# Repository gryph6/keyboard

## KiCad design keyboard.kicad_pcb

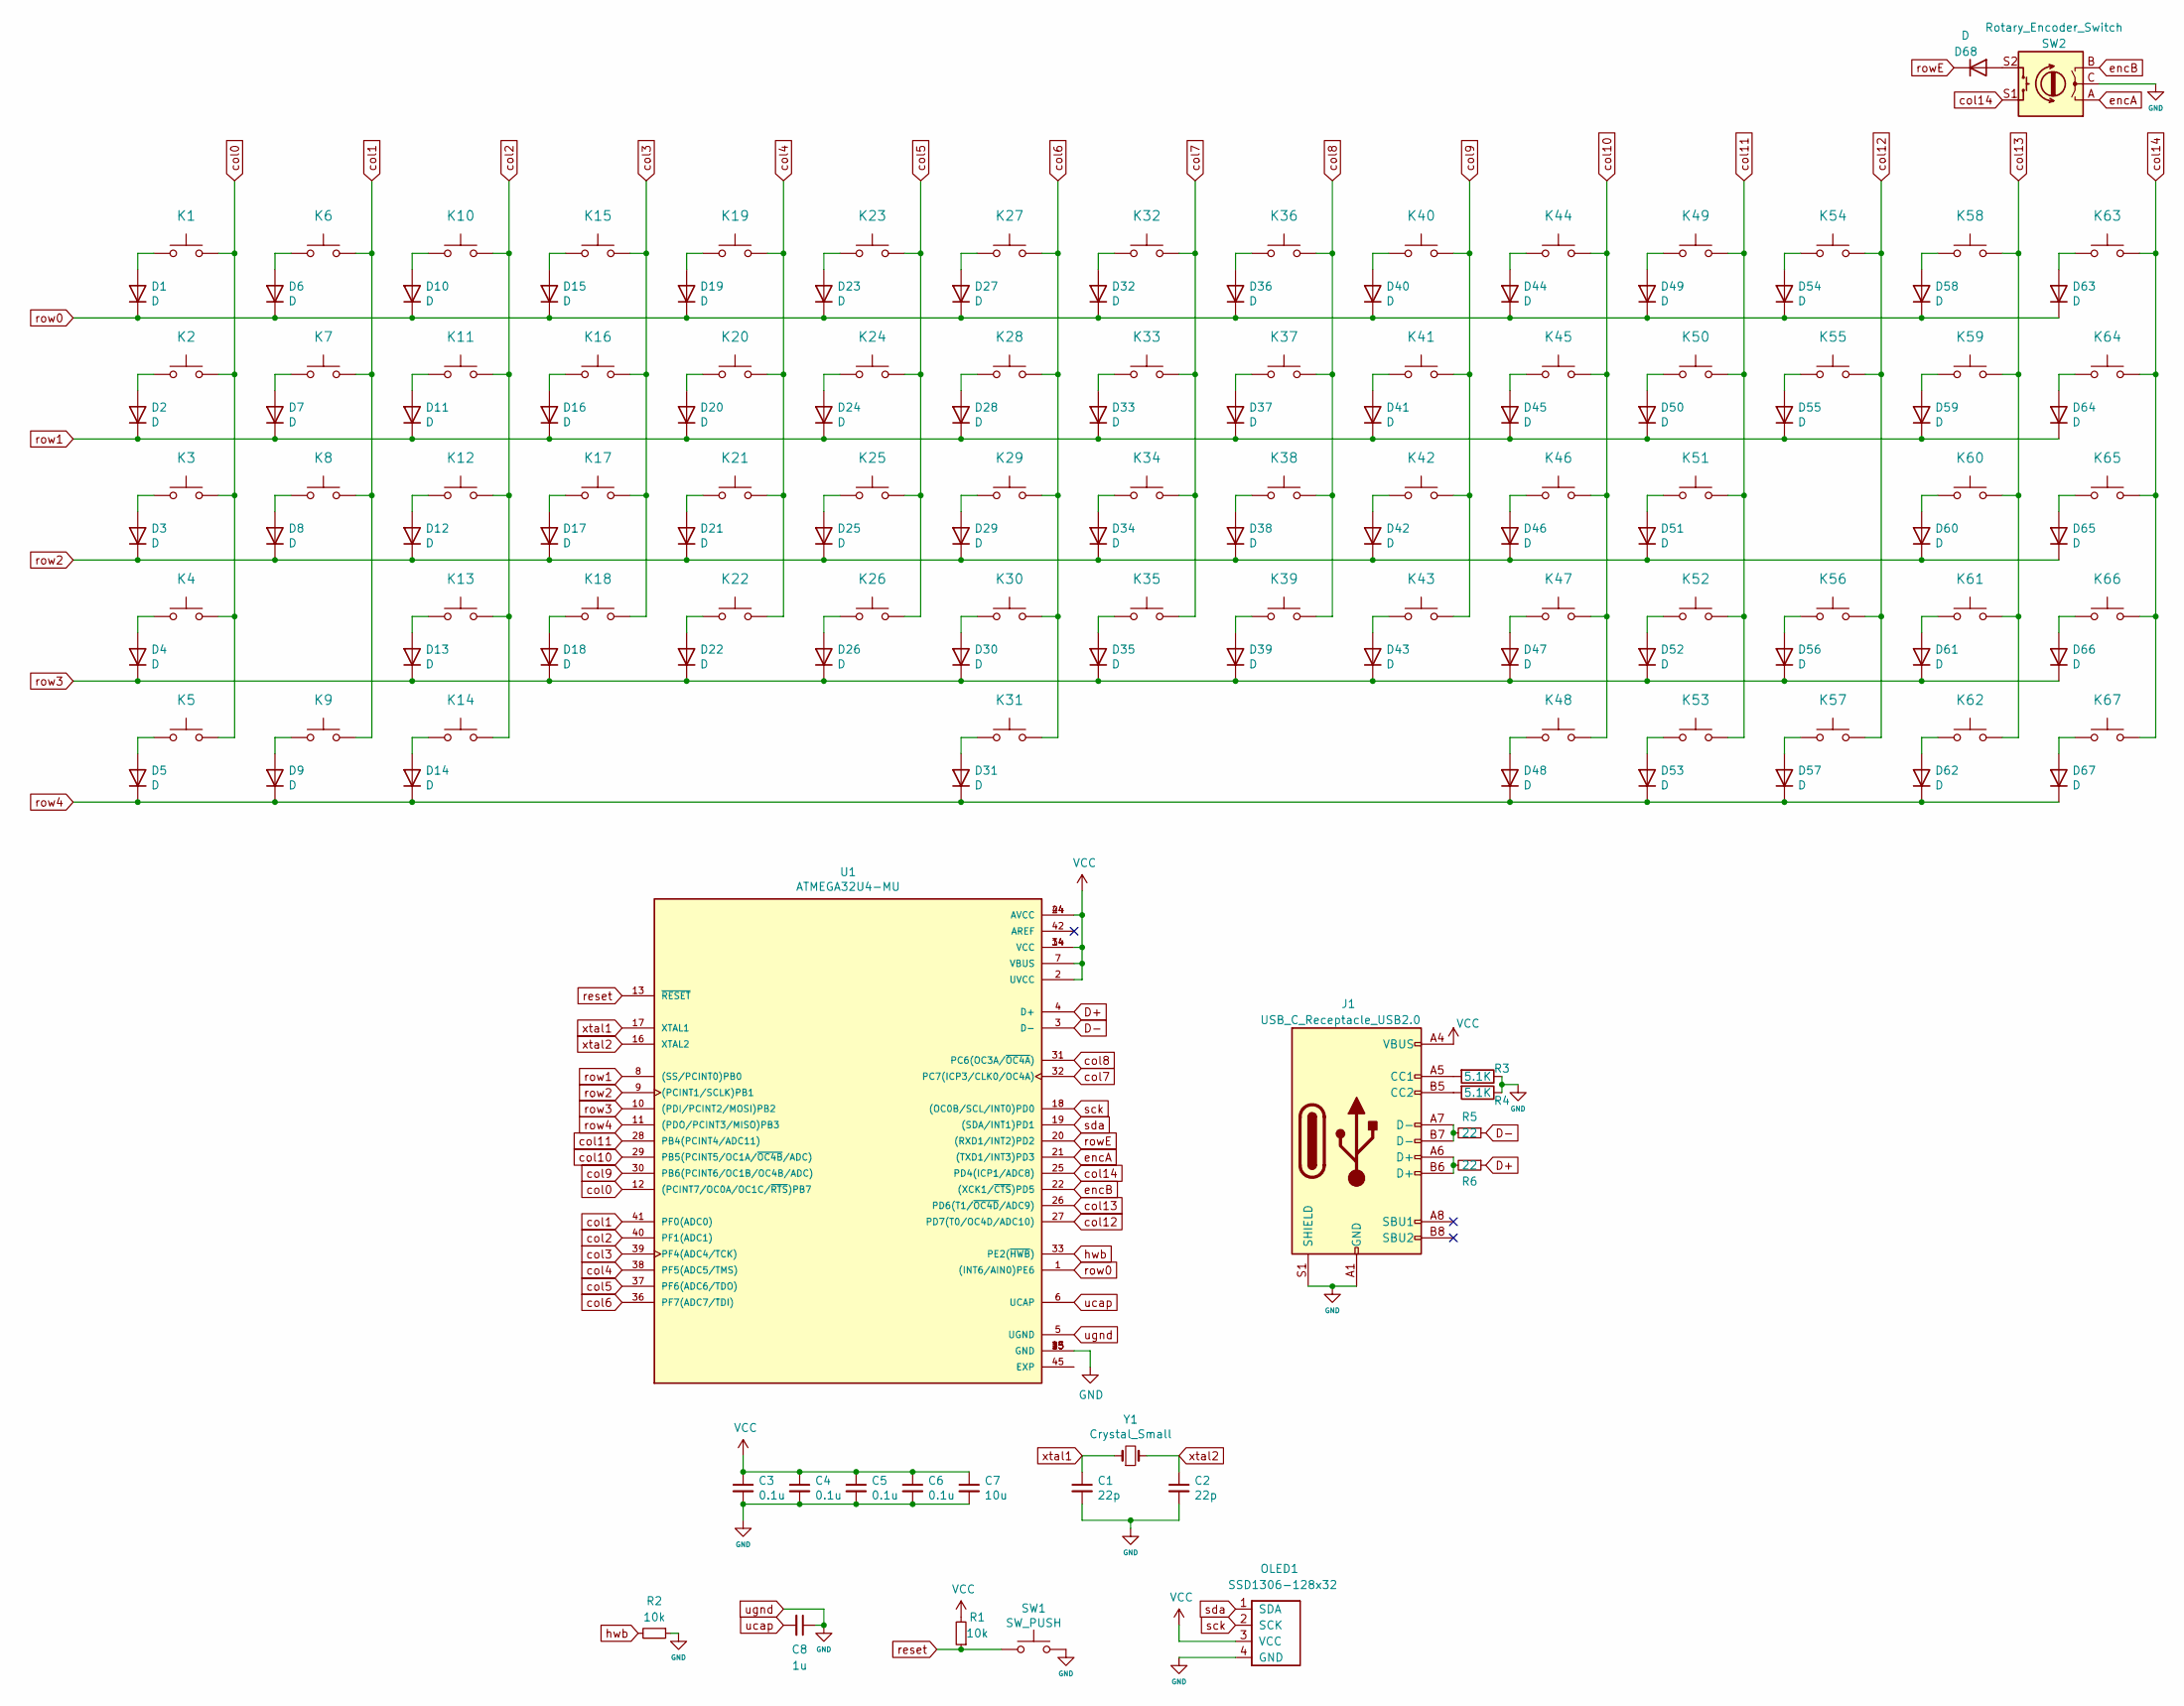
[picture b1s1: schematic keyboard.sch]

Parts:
C1, C2: 22p; C_0603_1608Metric
C3, C4, C5, C6: 0.1u; C_0603_1608Metric
C7: 10u; C_0603_1608Metric
C8: 1u; C_0603_1608Metric
D1, D2, D3, D4, D5, D6, D7, D8, D9, D10, D11, D12, D13, D14, D15, D16, D17, D18, D19, D20, D21, D22, D23, D24, D25, D26, D27, D28, D29, D30, D31, D32, D33, D34, D35, D36, D37, D38, D39, D40, D41, D42, D43, D44, D45, D46, D47, D48, D49, D50, D51, D52, D53, D54, D55, D56, D57, D58, D59, D60, D61, D62, D63, D64, D65, D66, D67, D68: D; D_SOD-323
J1: USB_C_Receptacle_USB2.0; USB_C_Receptacle_Amphenol_12401610E4-2A
K1, K6, K7, K8, K10, K11, K12, K13, K15, K16, K17, K18, K19, K20, K21, K22, K23, K24, K25, K26, K27, K28, K29, K30, K32, K33, K34, K35, K36, K37, K38, K39, K40, K41, K42, K43, K44, K45, K46, K47, K49, K50, K51, K52, K54, K55, K57, K61, K62, K63, K64, K65, K66, K67: KEYSW; SW_Cherry_MX_1.00u_PCB
K2, K59: KEYSW; SW_Cherry_MX_1.50u_PCB
K3, K56: KEYSW; SW_Cherry_MX_1.75u_PCB
K4, K60: KEYSW; SW_Cherry_MX_2.25u_PCB
K5, K9, K14, K48, K53: KEYSW; SW_Cherry_MX_1.25u_PCB
K31: KEYSW; SW_Cherry_MX_6.25u_PCB
K58: KEYSW; SW_Cherry_MX_2.00u_PCB
OLED1: SSD1306-128x32; OLED-SSD1306
R1, R2: 10k; R_0603_1608Metric
R3, R4: 5.1K; R_0603_1608Metric
R5, R6: 22; R_0603_1608Metric
SW1: SW_PUSH; SW_PUSH_6mm
SW2: Rotary_Encoder_Switch; RotaryEncoder_Alps_EC11E-Switch_Vertical_H20mm
U1: ATMEGA32U4-MU; QFN50P700X700X100-45N; PARTREV E
Y1: Crystal_Small; Crystal_SMD_3225-4Pin_3.2x2.5mm

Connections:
D+: R6.1, U1.4 (D+)
D-: R5.1, U1.3 (D-)
unnamed: D1.2 (A), K1.1
unnamed: D2.2 (A), K2.1
unnamed: D3.2 (A), K3.1
unnamed: D4.2 (A), K4.1
unnamed: D5.2 (A), K5.1
unnamed: D6.2 (A), K6.1
unnamed: D7.2 (A), K7.1
unnamed: D8.2 (A), K8.1
unnamed: D9.2 (A), K9.1
unnamed: D10.2 (A), K10.1
unnamed: D11.2 (A), K11.1
unnamed: D12.2 (A), K12.1
unnamed: D13.2 (A), K13.1
unnamed: D14.2 (A), K14.1
unnamed: D15.2 (A), K15.1
unnamed: D16.2 (A), K16.1
unnamed: D17.2 (A), K17.1
unnamed: D18.2 (A), K18.1
unnamed: D19.2 (A), K19.1
unnamed: D20.2 (A), K20.1
unnamed: D21.2 (A), K21.1
unnamed: D22.2 (A), K22.1
unnamed: D23.2 (A), K23.1
unnamed: D24.2 (A), K24.1
unnamed: D25.2 (A), K25.1
unnamed: D26.2 (A), K26.1
unnamed: D27.2 (A), K27.1
unnamed: D28.2 (A), K28.1
unnamed: D29.2 (A), K29.1
unnamed: D30.2 (A), K30.1
unnamed: D31.2 (A), K31.1
unnamed: D32.2 (A), K32.1
unnamed: D33.2 (A), K33.1
unnamed: D34.2 (A), K34.1
unnamed: D35.2 (A), K35.1
unnamed: D36.2 (A), K36.1
unnamed: D37.2 (A), K37.1
unnamed: D38.2 (A), K38.1
unnamed: D39.2 (A), K39.1
unnamed: D40.2 (A), K40.1
unnamed: D41.2 (A), K41.1
unnamed: D42.2 (A), K42.1
unnamed: D43.2 (A), K43.1
unnamed: D44.2 (A), K44.1
unnamed: D45.2 (A), K45.1
unnamed: D46.2 (A), K46.1
unnamed: D47.2 (A), K47.1
unnamed: D48.2 (A), K48.1
unnamed: D49.2 (A), K49.1
unnamed: D50.2 (A), K50.1
unnamed: D51.2 (A), K51.1
unnamed: D52.2 (A), K52.1
unnamed: D53.2 (A), K53.1
unnamed: D54.2 (A), K54.1
unnamed: D55.2 (A), K55.1
unnamed: D56.2 (A), K56.1
unnamed: D57.2 (A), K57.1
unnamed: D58.2 (A), K58.1
unnamed: D59.2 (A), K59.1
unnamed: D60.2 (A), K60.1
unnamed: D61.2 (A), K61.1
unnamed: D62.2 (A), K62.1
unnamed: D63.2 (A), K63.1
unnamed: D64.2 (A), K64.1
unnamed: D65.2 (A), K65.1
unnamed: D66.2 (A), K66.1
unnamed: D67.2 (A), K67.1
unnamed: D68.2 (A), SW2.S2
unnamed: J1.A5 (CC1), R3.2
unnamed: J1.A6 (D+), J1.B6 (D+), R6.2
unnamed: J1.A7 (D-), J1.B7 (D-), R5.2
unnamed: J1.B5 (CC2), R4.2
VCC: C3.1, C4.1, C5.1, C6.1, C7.1, J1.A4 (VBUS), J1.A9 (VBUS), J1.B4 (VBUS), J1.B9 (VBUS), OLED1.3 (VCC), R1.2, U1.2 (UVCC), U1.7 (VBUS), U1.14 (VCC), U1.24 (AVCC), U1.34 (VCC), U1.44 (AVCC)
col0: K1.2, K2.2, K3.2, K4.2, K5.2, U1.12 ((PCINT7/OC0A/OC1C/~RTS~)PB7)
col1: K6.2, K7.2, K8.2, K9.2, U1.41 (PF0(ADC0))
col2: K10.2, K11.2, K12.2, K13.2, K14.2, U1.40 (PF1(ADC1))
col3: K15.2, K16.2, K17.2, K18.2, U1.39 (PF4(ADC4/TCK))
col4: K19.2, K20.2, K21.2, K22.2, U1.38 (PF5(ADC5/TMS))
col5: K23.2, K24.2, K25.2, K26.2, U1.37 (PF6(ADC6/TDO))
col6: K27.2, K28.2, K29.2, K30.2, K31.2, U1.36 (PF7(ADC7/TDI))
col7: K32.2, K33.2, K34.2, K35.2, U1.32 (PC7(ICP3/CLK0/OC4A))
col8: K36.2, K37.2, K38.2, K39.2, U1.31 (PC6(OC3A/~OC4A~))
col9: K40.2, K41.2, K42.2, K43.2, U1.30 (PB6(PCINT6/OC1B/OC4B/ADC))
col10: K44.2, K45.2, K46.2, K47.2, K48.2, U1.29 (PB5(PCINT5/OC1A/~OC4B~/ADC))
col11: K49.2, K50.2, K51.2, K52.2, K53.2, U1.28 (PB4(PCINT4/ADC11))
col12: K54.2, K55.2, K56.2, K57.2, U1.27 (PD7(T0/OC4D/ADC10))
col13: K58.2, K59.2, K60.2, K61.2, K62.2, U1.26 (PD6(T1/~OC4D~/ADC9))
col14: K63.2, K64.2, K65.2, K66.2, K67.2, SW2.S1, U1.25 (PD4(ICP1/ADC8))
encA: SW2.A, U1.21 ((TXD1/INT3)PD3)
encB: SW2.B, U1.22 ((XCK1/~CTS~)PD5)
hwb: R2.2, U1.33 (PE2(~HWB~))
reset: R1.1, SW1.1, U1.13 (~RESET~)
row0: D1.1 (K), D6.1 (K), D10.1 (K), D15.1 (K), D19.1 (K), D23.1 (K), D27.1 (K), D32.1 (K), D36.1 (K), D40.1 (K), D44.1 (K), D49.1 (K), D54.1 (K), D58.1 (K), D63.1 (K), U1.1 ((INT6/AIN0)PE6)
row1: D2.1 (K), D7.1 (K), D11.1 (K), D16.1 (K), D20.1 (K), D24.1 (K), D28.1 (K), D33.1 (K), D37.1 (K), D41.1 (K), D45.1 (K), D50.1 (K), D55.1 (K), D59.1 (K), D64.1 (K), U1.8 ((SS/PCINT0)PB0)
row2: D3.1 (K), D8.1 (K), D12.1 (K), D17.1 (K), D21.1 (K), D25.1 (K), D29.1 (K), D34.1 (K), D38.1 (K), D42.1 (K), D46.1 (K), D51.1 (K), D60.1 (K), D65.1 (K), U1.9 ((PCINT1/SCLK)PB1)
row3: D4.1 (K), D13.1 (K), D18.1 (K), D22.1 (K), D26.1 (K), D30.1 (K), D35.1 (K), D39.1 (K), D43.1 (K), D47.1 (K), D52.1 (K), D56.1 (K), D61.1 (K), D66.1 (K), U1.10 ((PDI/PCINT2/MOSI)PB2)
row4: D5.1 (K), D9.1 (K), D14.1 (K), D31.1 (K), D48.1 (K), D53.1 (K), D57.1 (K), D62.1 (K), D67.1 (K), U1.11 ((PDO/PCINT3/MISO)PB3)
rowE: D68.1 (K), U1.20 ((RXD1/INT2)PD2)
sck: OLED1.2 (SCK), U1.18 ((OC0B/SCL/INT0)PD0)
sda: OLED1.1 (SDA), U1.19 ((SDA/INT1)PD1)
ucap: C8.2, U1.6 (UCAP)
ugnd: C1.2, C2.2, C3.2, C4.2, C5.2, C6.2, C7.2, C8.1, J1.A1 (GND), J1.A12 (GND), J1.B1 (GND), J1.B12 (GND), J1.S1 (SHIELD), OLED1.4 (GND), R2.1, R3.1, R4.1, SW1.2, SW2.C, U1.5 (UGND), U1.15 (GND), U1.23 (GND), U1.35 (GND), U1.43 (GND)
xtal1: C1.1, U1.17 (XTAL1), Y1.1
xtal2: C2.1, U1.16 (XTAL2), Y1.2

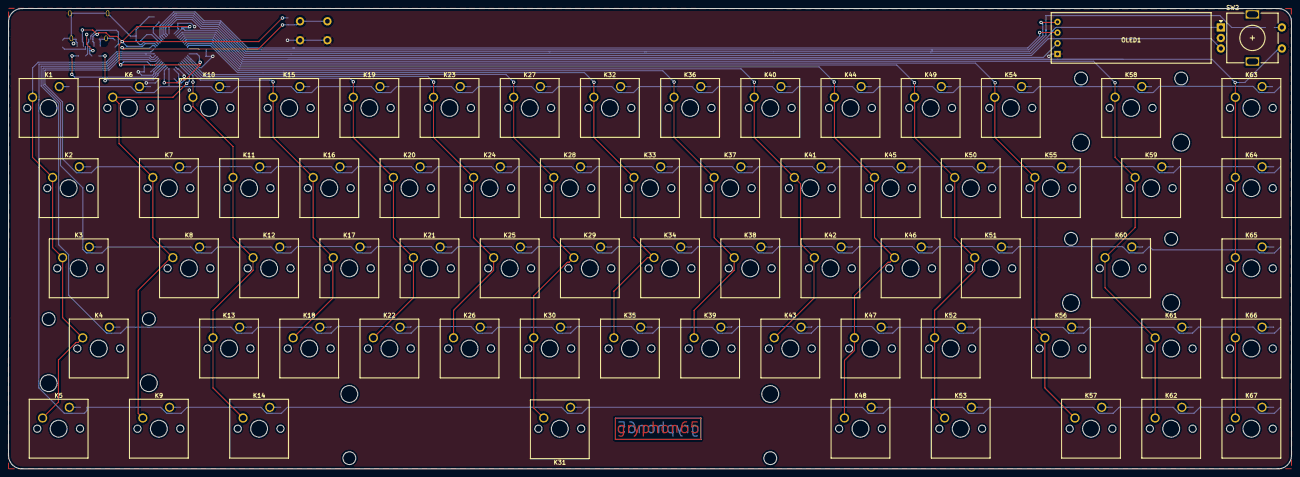
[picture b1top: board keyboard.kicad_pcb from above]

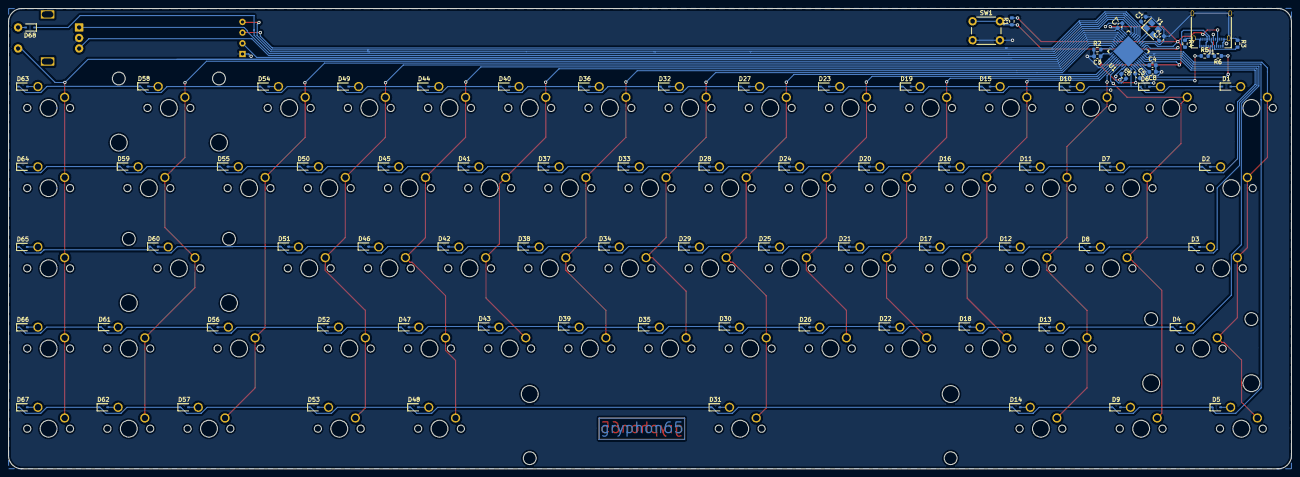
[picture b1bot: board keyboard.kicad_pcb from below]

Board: 2 copper layers, 304.8 x 109.3 mm, 155 parts (86 on the bottom side), 106 nets.

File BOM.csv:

Id,Designator,Package,Quantity,Designation,Supplier and ref,1sets,Part No.
1,"D68,D1,D2,D3,D4,D5,D6,D7,D8,D9,D10,D11,D12,D13,D14,D15,D16,D17,D18,D19,D20,D21,D22,D23,D24,D25,D26,D27,D28,D29,D30,D31,D32,D33,D34,D35,D36,D37,D38,D39,D40,D41,D42,D43,D53,D44,D45,D46,D47,D48,D49,D50,D51,D52,D54,D55,D56,D57,D58,D59,D60,D61,D62,D64,D65,D66,D67,D63",D_0603_1608Metric,68,D,Taiwan Semiconductor Corporation,,TS4148C RZG
2,K31,SW_Cherry_MX_6.25u_PCB,1,KEYSW,NO ASSEMBLY,,NO ASSEMBLY
3,C8,C_0603_1608Metric,1,1u,KEMET,,C0603C105K4RACTU
4,J1,USB_C_Receptacle_Amphenol_12401610E4-2A,1,USB_C_Receptacle_USB2.0,Amphenol ICC,$2.73 ,12401610E4#2A 7-10work days
5,Y1,Crystal_SMD_3225-4Pin_3.2x2.5mm,1,Crystal_Small,"NDK America, Inc.",,NX3225SA-16.000000MHZ-T1
6,OLED1,OLED-SSD1306,1,SSD1306-128x32,NO ASSEMBLY,,NO ASSEMBLY
7,"K54,K1,K6,K7,K8,K10,K11,K12,K13,K15,K16,K17,K18,K19,K20,K21,K22,K23,K24,K25,K26,K27,K28,K29,K30,K32,K33,K34,K35,K36,K37,K38,K39,K40,K41,K42,K43,K44,K45,K46,K47,K49,K50,K51,K52,K55,K57,K61,K62,K64,K65,K66,K67,K63",SW_Cherry_MX_1.00u_PCB,54,KEYSW,NO ASSEMBLY,,NO ASSEMBLY
8,"C1,C2",C_0603_1608Metric,2,22p,KEMET,,C0603C220K4GACTU
9,"C3,C4,C5,C6",C_0603_1608Metric,4,0.1u,KEMET,,C0603C104K4RACTU
10,C7,C_0603_1608Metric,1,10u,KEMET,,C0603C106M8PAC7867
11,"K2,K59",SW_Cherry_MX_1.50u_PCB,2,KEYSW,NO ASSEMBLY,,NO ASSEMBLY
12,"K3,K56",SW_Cherry_MX_1.75u_PCB,2,KEYSW,NO ASSEMBLY,,NO ASSEMBLY
13,"K4,K60",SW_Cherry_MX_2.25u_PCB,2,KEYSW,NO ASSEMBLY,,NO ASSEMBLY
14,"K5,K9,K14,K53,K48",SW_Cherry_MX_1.25u_PCB,5,KEYSW,NO ASSEMBLY,,NO ASSEMBLY
15,K58,SW_Cherry_MX_2.00u_PCB,1,KEYSW,NO ASSEMBLY,,NO ASSEMBLY
16,SW1,SW_PUSH_6mm,1,SW_PUSH,NO ASSEMBLY,,NO ASSEMBLY
17,"R1,R2",R_0603_1608Metric,2,10k,Yageo,,RC0603FR-0710KL
18,"R3,R4",R_0603_1608Metric,2,5.1K,Yageo,,RC0603FR-075K1L
19,"R5,R6",R_0603_1608Metric,2,22,Yageo,,RC0603FR-0722RL
20,U1,QFN50P700X700X100-45N,1,ATMEGA32U4-MU,,$6.51 ,7-10work days
21,SW2,RotaryEncoder_Alps_EC11E-Switch_Vertical_H20mm,1,Rotary_Encoder_Switch,NO ASSEMBLY,,NO ASSEMBLY
,,,,,,,
,,,,,,,
,,,,,,,
,,,,,,Per Designation,

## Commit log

2021-04-07 keyboard
2021-04-07 move to global labels
2021-04-07 add 5v and gnd lines
2021-04-07 add oled
2021-04-07 upload
2021-04-10 add git ignore
2021-04-10 organization
2021-04-10 position diodes
2021-04-17 routing
2021-04-19 routing, drc
2021-04-19 add keyboard cache
2021-04-20 one more connection
2021-04-20 finished. :)
2021-04-20 jk now I'm done
2021-04-20 move folders
2021-05-12 finishing files
2021-05-12 add kle
